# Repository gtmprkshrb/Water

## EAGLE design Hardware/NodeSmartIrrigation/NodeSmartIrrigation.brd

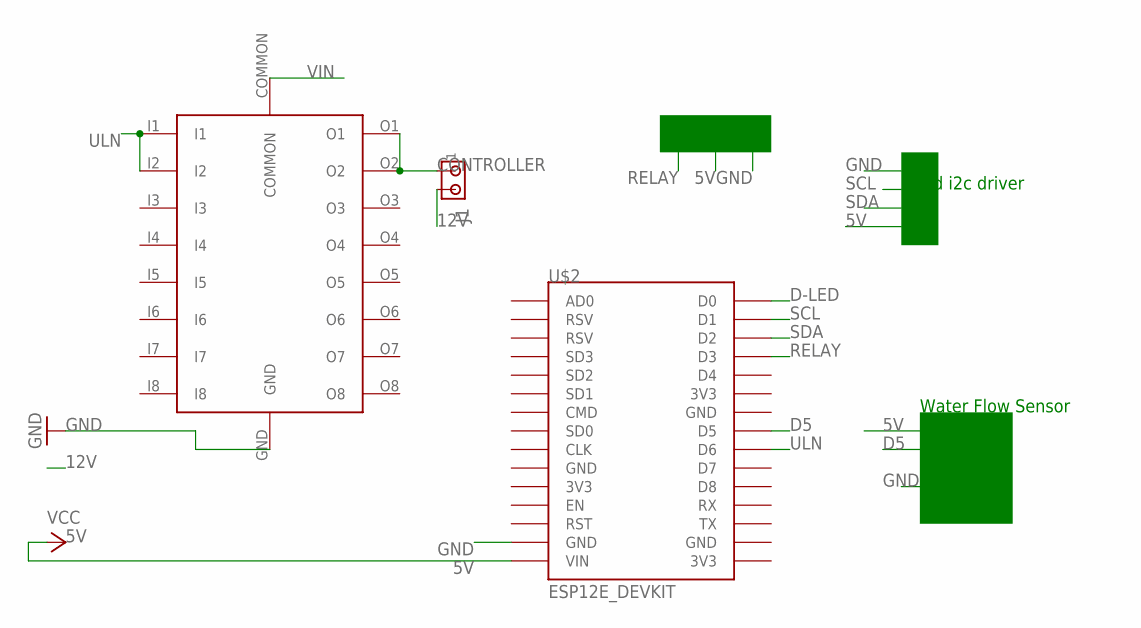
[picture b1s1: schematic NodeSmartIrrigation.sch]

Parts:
J1: MTA02-100; 10X02MTA
U$1: ULN2803AFWG
U$2: ESP12E_DEVKIT

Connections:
5V: U$2.VIN
12V: J1.2
CONTROLLER: J1.1, U$1.O1, U$1.O2
D5: U$2.D5
D-LED: U$2.D0
GND: U$1.GND, U$2.GND@1 (GND)
RELAY: U$2.D3
SCL: U$2.D1
SDA: U$2.D2
ULN: U$1.I1, U$1.I2, U$2.D6
VIN: U$1.COMMON

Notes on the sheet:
lcd i2c driver
DHT
Water Flow Sensor

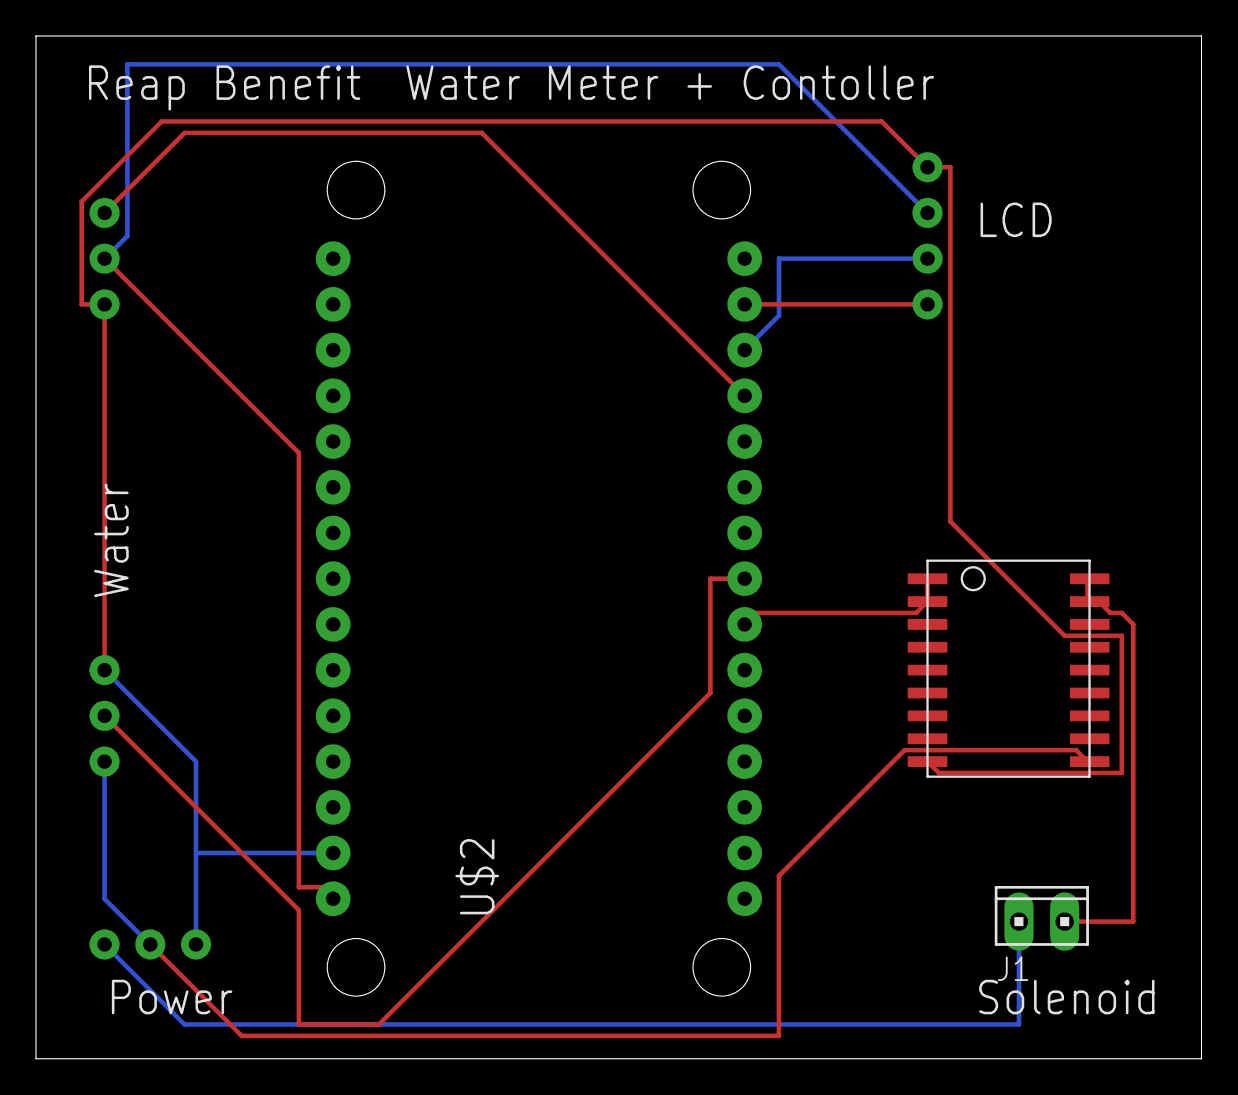
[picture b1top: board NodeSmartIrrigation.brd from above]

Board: 2 copper layers, 64.8 x 56.8 mm, 3 parts (0 on the bottom side), 3 nets.

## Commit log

2017-01-16 :boom::camel: Added .gitattributes & .gitignore files
2017-03-28 Updated with 3 codes
